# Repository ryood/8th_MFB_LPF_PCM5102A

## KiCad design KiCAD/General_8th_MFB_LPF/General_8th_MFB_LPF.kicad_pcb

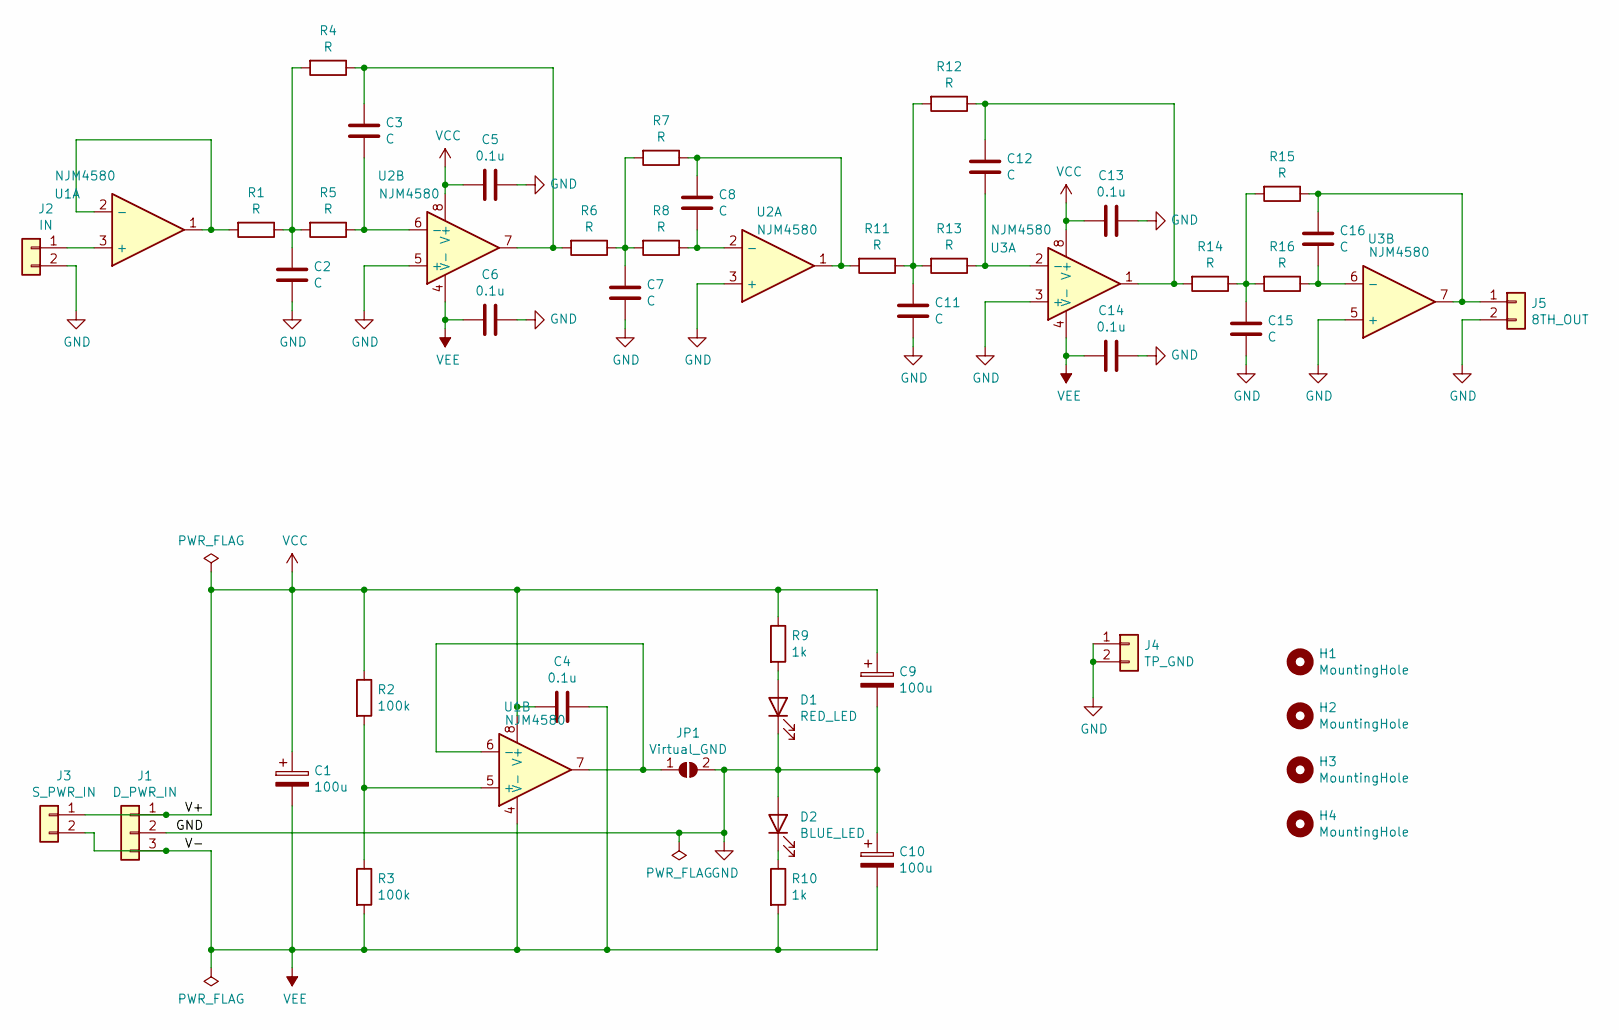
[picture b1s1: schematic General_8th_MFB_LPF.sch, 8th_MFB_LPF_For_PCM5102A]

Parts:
C1, C9, C10: 100u; CP_Radial_D6.3mm_P2.50mm
C2, C3, C7, C8, C11, C12, C15, C16: C; C_Rect_L7.0mm_W3.5mm_P2.50mm_P5.00mm
C4, C5, C6, C13, C14: 0.1u; C_Disc_D3.4mm_W2.1mm_P2.50mm
D1: RED_LED; LED_D3.0mm
D2: BLUE_LED; LED_D3.0mm
H1, H2, H3, H4: MountingHole; MountingHole_3.2mm_M3
J1: D_PWR_IN; JST_XH_B3B-XH-A_1x03_P2.50mm_Vertical
J2: IN; JST_XH_B2B-XH-A_1x02_P2.50mm_Vertical
J3: S_PWR_IN; JST_XH_B2B-XH-A_1x02_P2.50mm_Vertical
J4: TP_GND; PinHeader_1x02_P2.54mm_Vertical
J5: 8TH_OUT; JST_XH_B2B-XH-A_1x02_P2.50mm_Vertical
JP1: Virtual_GND; SolderJumper-2_P1.3mm_Open_RoundedPad1.0x1.5mm
R1, R4, R5, R6, R7, R8, R11, R12, R13, R14, R15, R16: R; R_Axial_DIN0207_L6.3mm_D2.5mm_P7.62mm_Horizontal
R2, R3: 100k; R_Axial_DIN0207_L6.3mm_D2.5mm_P7.62mm_Horizontal
R9, R10: 1k; R_Axial_DIN0207_L6.3mm_D2.5mm_P7.62mm_Horizontal
U1, U2, U3: NJM4580; DIP-8_W7.62mm_Socket_LongPads

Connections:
GND: C2.2, C5.1, C6.1, C7.2, C9.2, C10.1, C11.2, C13.1, C14.1, C15.2, D1.1 (K), D2.2 (A), J1.2, J2.2, J4.1, J4.2, J5.2, JP1.2 (B), U2.3 (+), U2.5 (+), U3.3 (+), U3.5 (+)
unnamed: C2.1, R1.1, R4.2, R5.2
unnamed: C3.1, R4.1, R6.2, U2.7
unnamed: C3.2, R5.1, U2.6 (-)
unnamed: C7.1, R6.1, R7.2, R8.2
unnamed: C8.1, R7.1, R11.2, U2.1
unnamed: C8.2, R8.1, U2.2 (-)
unnamed: C11.1, R11.1, R12.2, R13.2
unnamed: C12.1, R12.1, R14.2, U3.1
unnamed: C12.2, R13.1, U3.2 (-)
unnamed: C15.1, R14.1, R15.2, R16.2
unnamed: C16.1, J5.1, R15.1, U3.7
unnamed: C16.2, R16.1, U3.6 (-)
unnamed: D1.2 (A), R9.2
unnamed: D2.1 (K), R10.1
unnamed: J2.1, U1.3 (+)
unnamed: JP1.1 (A), U1.6 (-), U1.7
unnamed: R1.2, U1.1, U1.2 (-)
unnamed: R2.2, R3.1, U1.5 (+)
VCC: C1.1, C4.2, C5.2, C9.1, C13.2, J1.1, J3.1, R2.1, R9.1, U1.8 (V+), U2.8 (V+), U3.8 (V+)
VEE: C1.2, C4.1, C6.2, C10.2, C14.2, J1.3, J3.2, R3.2, R10.2, U1.4 (V-), U2.4 (V-), U3.4 (V-)

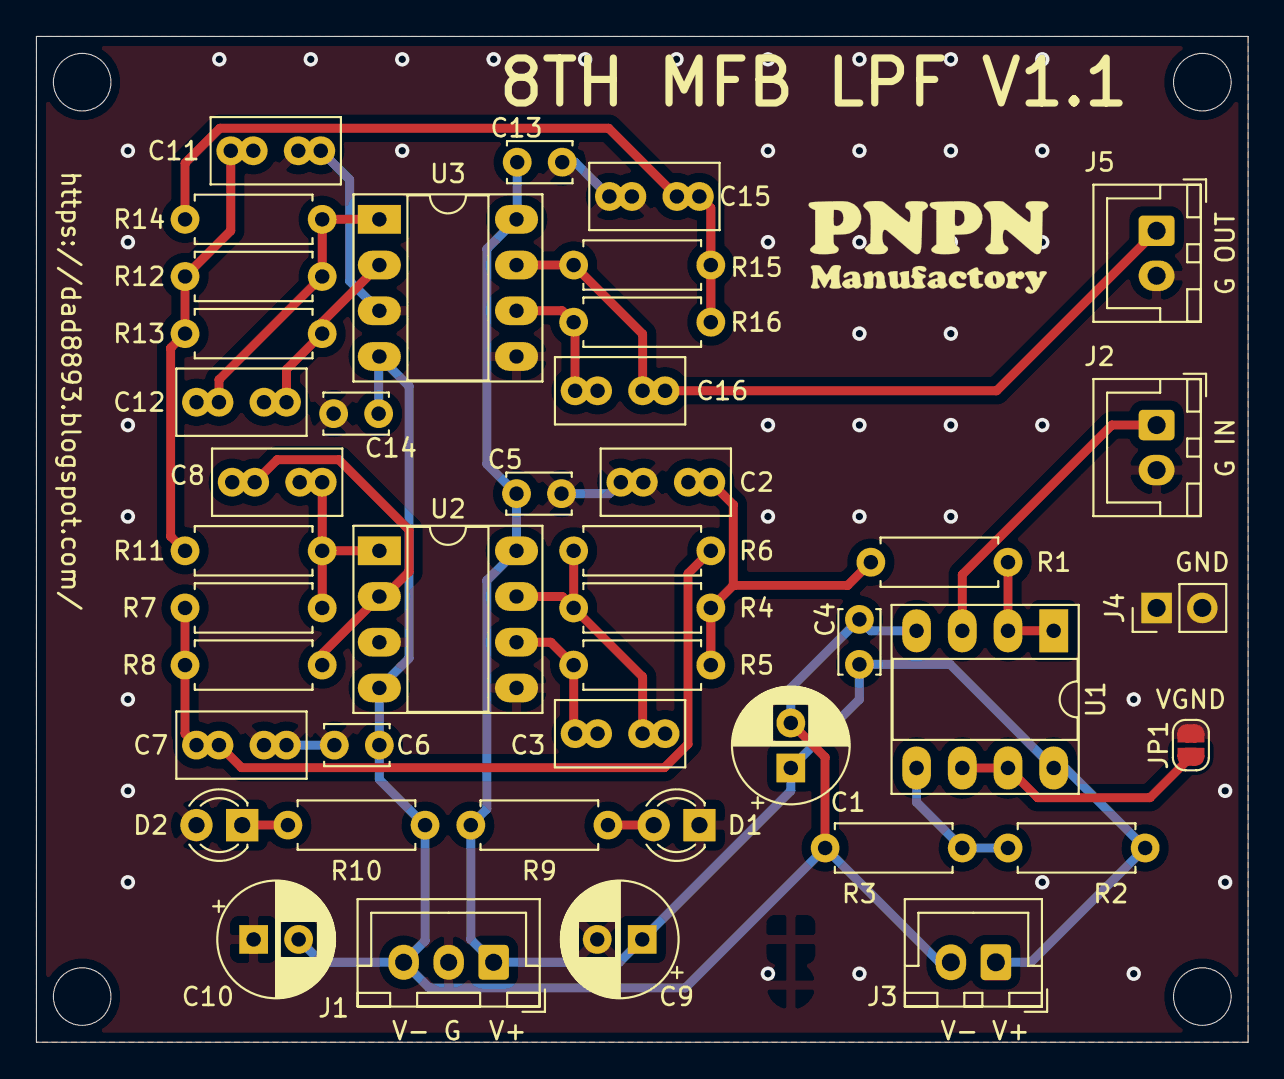
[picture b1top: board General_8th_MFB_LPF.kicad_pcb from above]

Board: 2 copper layers, 67.3 x 55.9 mm, 47 parts (0 on the bottom side), 21 nets.

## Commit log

2020-11-13 Add Buffer
2020-11-13 PCB Design
2020-11-30 Update: PCB Design
